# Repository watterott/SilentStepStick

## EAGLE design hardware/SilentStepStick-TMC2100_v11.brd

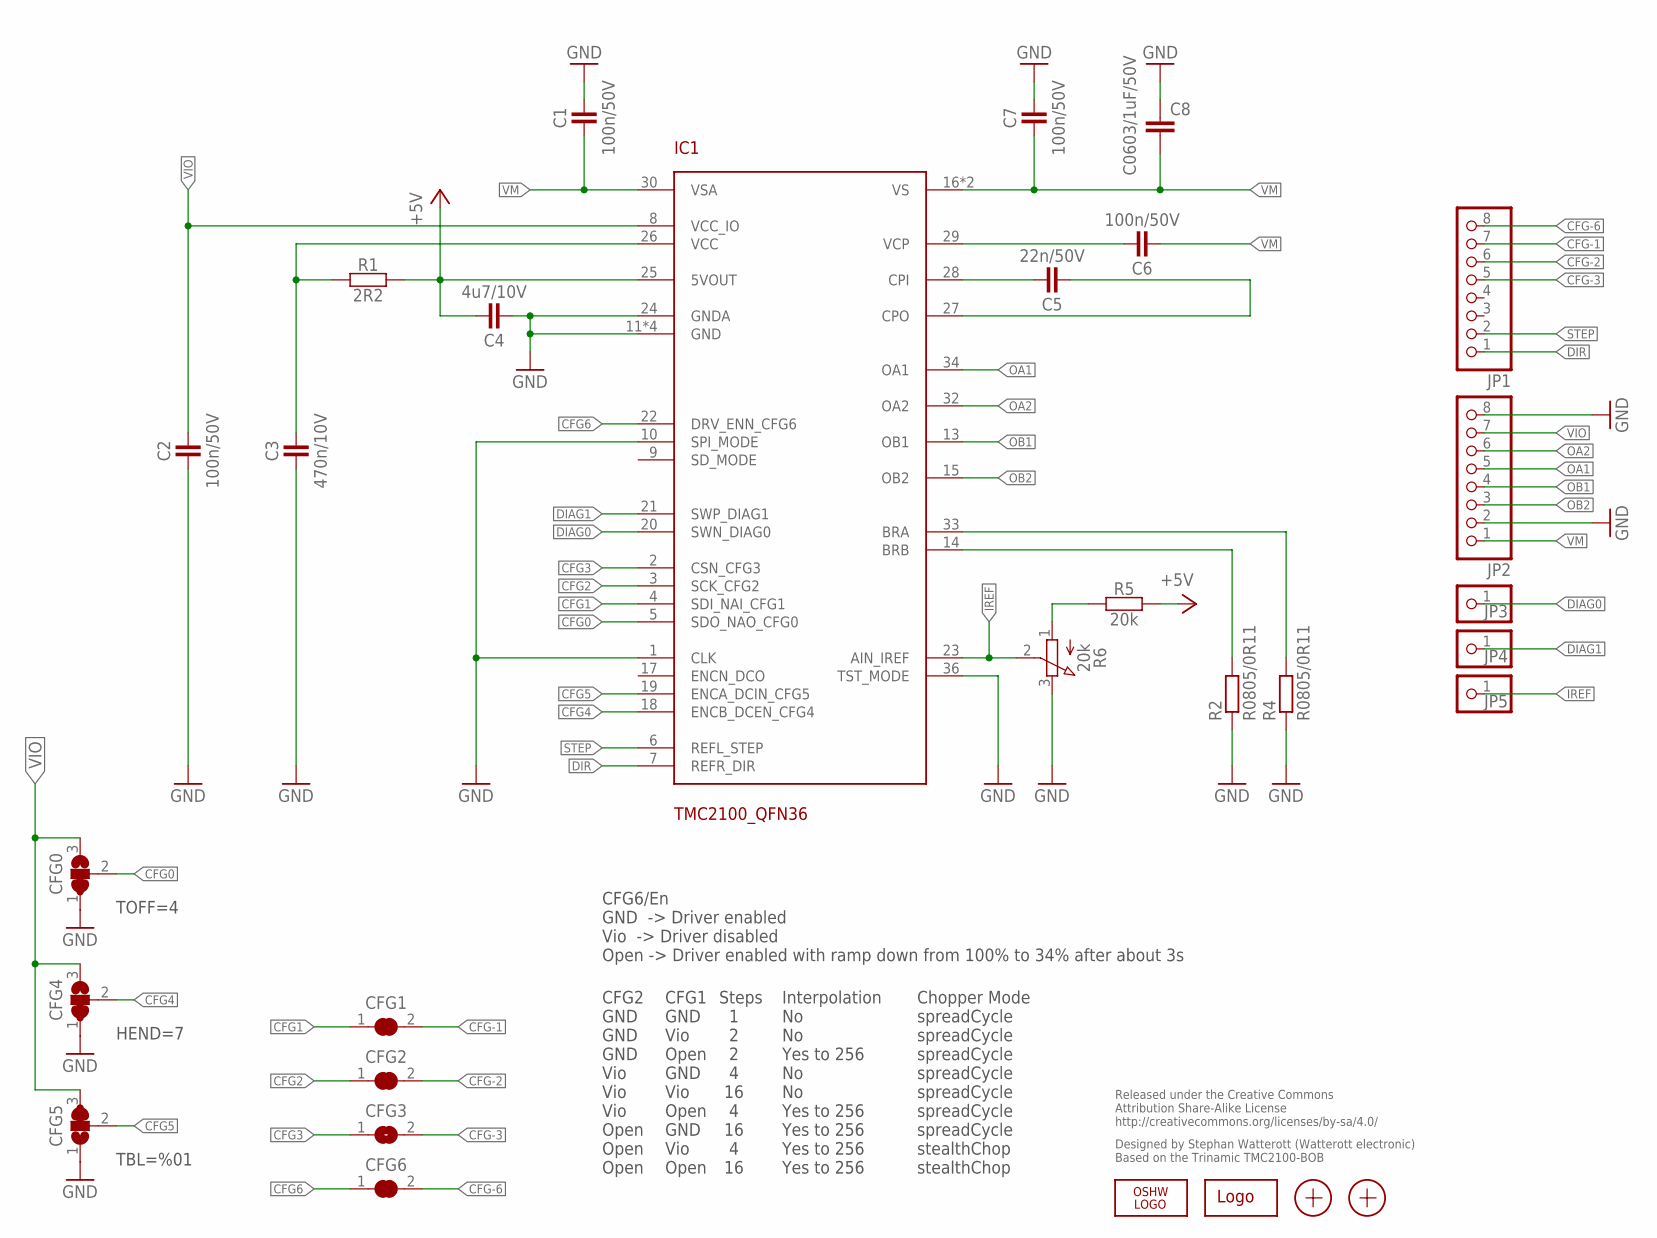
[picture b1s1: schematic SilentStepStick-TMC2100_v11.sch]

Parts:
C1, C2, C6, C7: 100n/50V; R0402
C3: 470n/10V; R0402
C4: 4u7/10V; R0402
C5: 22n/50V; R0402
C8: C0603/1uF/50V; C0603
CFG0, CFG4, CFG5: JUMPER3-0201
CFG1, CFG2, CFG3, CFG6: JUMPER2-0201
IC1: TMC2100_QFN36; QFN36
JP1, JP2: PINHD-1X08_2.54-S; 1X08-S
JP3, JP4, JP5: PINHD-1X1; 1X01
LOGO1: OSHW_LOGOX0070; OSHW_6X70
LOGO2: LOGO-S_PLACE_M; SPARK_TPLACE_M
R1: 2R2; R0402
R2, R4: R0805/0R11; M0805
R5: 20k; R0402
R6: 20k; POT_EVM3R
X1, X2: PASSER-07; PASSER_07MM

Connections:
+5V: C4.2, IC1.25 (5VOUT), R1.2, R5.2
CFG0: CFG0.2, IC1.5 (SDO_NAO_CFG0)
CFG1: CFG1.1, IC1.4 (SDI_NAI_CFG1)
CFG2: CFG2.1, IC1.3 (SCK_CFG2)
CFG3: CFG3.1, IC1.2 (CSN_CFG3)
CFG4: CFG4.2, IC1.18 (ENCB_DCEN_CFG4)
CFG5: CFG5.2, IC1.19 (ENCA_DCIN_CFG5)
CFG6: CFG6.1, IC1.22 (DRV_ENN_CFG6)
CFG-1: CFG1.2, JP1.7
CFG-2: CFG2.2, JP1.6
CFG-3: CFG3.2, JP1.5
CFG-6: CFG6.2, JP1.8
CPI: C5.2, IC1.28 (CPI)
CPO: C5.1, IC1.27 (CPO)
DIAG0: IC1.20 (SWN_DIAG0), JP3.1
DIAG1: IC1.21 (SWP_DIAG1), JP4.1
DIR: IC1.7 (REFR_DIR), JP1.1
GND: C1.2, C2.1, C3.1, C4.1, C7.2, C8.2, CFG0.1, CFG4.1, CFG5.1, IC1.1 (CLK), IC1.10 (SPI_MODE), IC1.11 (GND), IC1.12 (GND), IC1.24 (GNDA), IC1.35 (GND), IC1.36 (TST_MODE), IC1.GND_PAD (GND), JP2.2, JP2.8, R2.1, R4.1, R6.3 (E)
IREF: IC1.23 (AIN_IREF), JP5.1, R6.2 (S)
unnamed: IC1.33 (BRA), R4.2
unnamed: IC1.14 (BRB), R2.2
OA1: IC1.34 (OA1), JP2.5
OA2: IC1.32 (OA2), JP2.6
OB1: IC1.13 (OB1), JP2.4
OB2: IC1.15 (OB2), JP2.3
STEP: IC1.6 (REFL_STEP), JP1.2
VCC: C3.2, IC1.26 (VCC), R1.1
VCP: C6.2, IC1.29 (VCP)
VIO: C2.2, CFG0.3, CFG4.3, CFG5.3, IC1.8 (VCC_IO), JP2.7
VM: C1.1, C6.1, C7.1, C8.1, IC1.16 (VS), IC1.30 (VSA), IC1.31 (VS), JP2.1
VREF1: R5.1, R6.1 (A)

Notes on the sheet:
Released under the Creative Commons Attribution Share-Alike License http://creativecommons.org/licenses/by-sa/4.0/
Designed by Stephan Watterott (Watterott electronic) Based on the Trinamic TMC2100-BOB
CFG6/En GND -> Driver enabled Vio -> Driver disabled Open -> Driver enabled with ramp down from 100% to 34% after about 3s
CFG2 GND GND GND Vio Vio Vio Open Open Open
CFG1 GND Vio Open GND Vio Open GND Vio Open
Steps 1 2 2 4 16 4 16 4 16
Interpolation No No Yes to 256 No No Yes to 256 Yes to 256 Yes to 256 Yes to 256
Chopper Mode spreadCycle spreadCycle spreadCycle spreadCycle spreadCycle spreadCycle spreadCycle stealthChop stealthChop
TOFF=4
HEND=7
TBL=%01

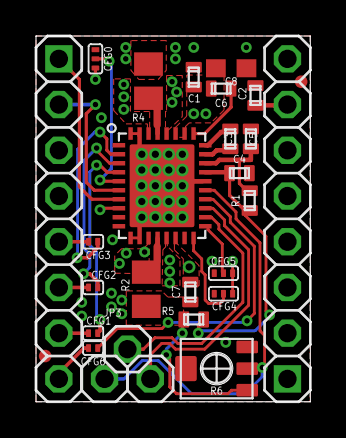
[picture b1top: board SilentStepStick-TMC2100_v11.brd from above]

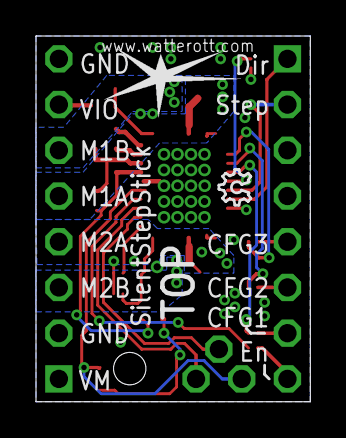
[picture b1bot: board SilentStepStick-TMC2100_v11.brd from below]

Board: 4 copper layers, 15.2 x 20.3 mm, 30 parts (2 on the bottom side), 31 nets.

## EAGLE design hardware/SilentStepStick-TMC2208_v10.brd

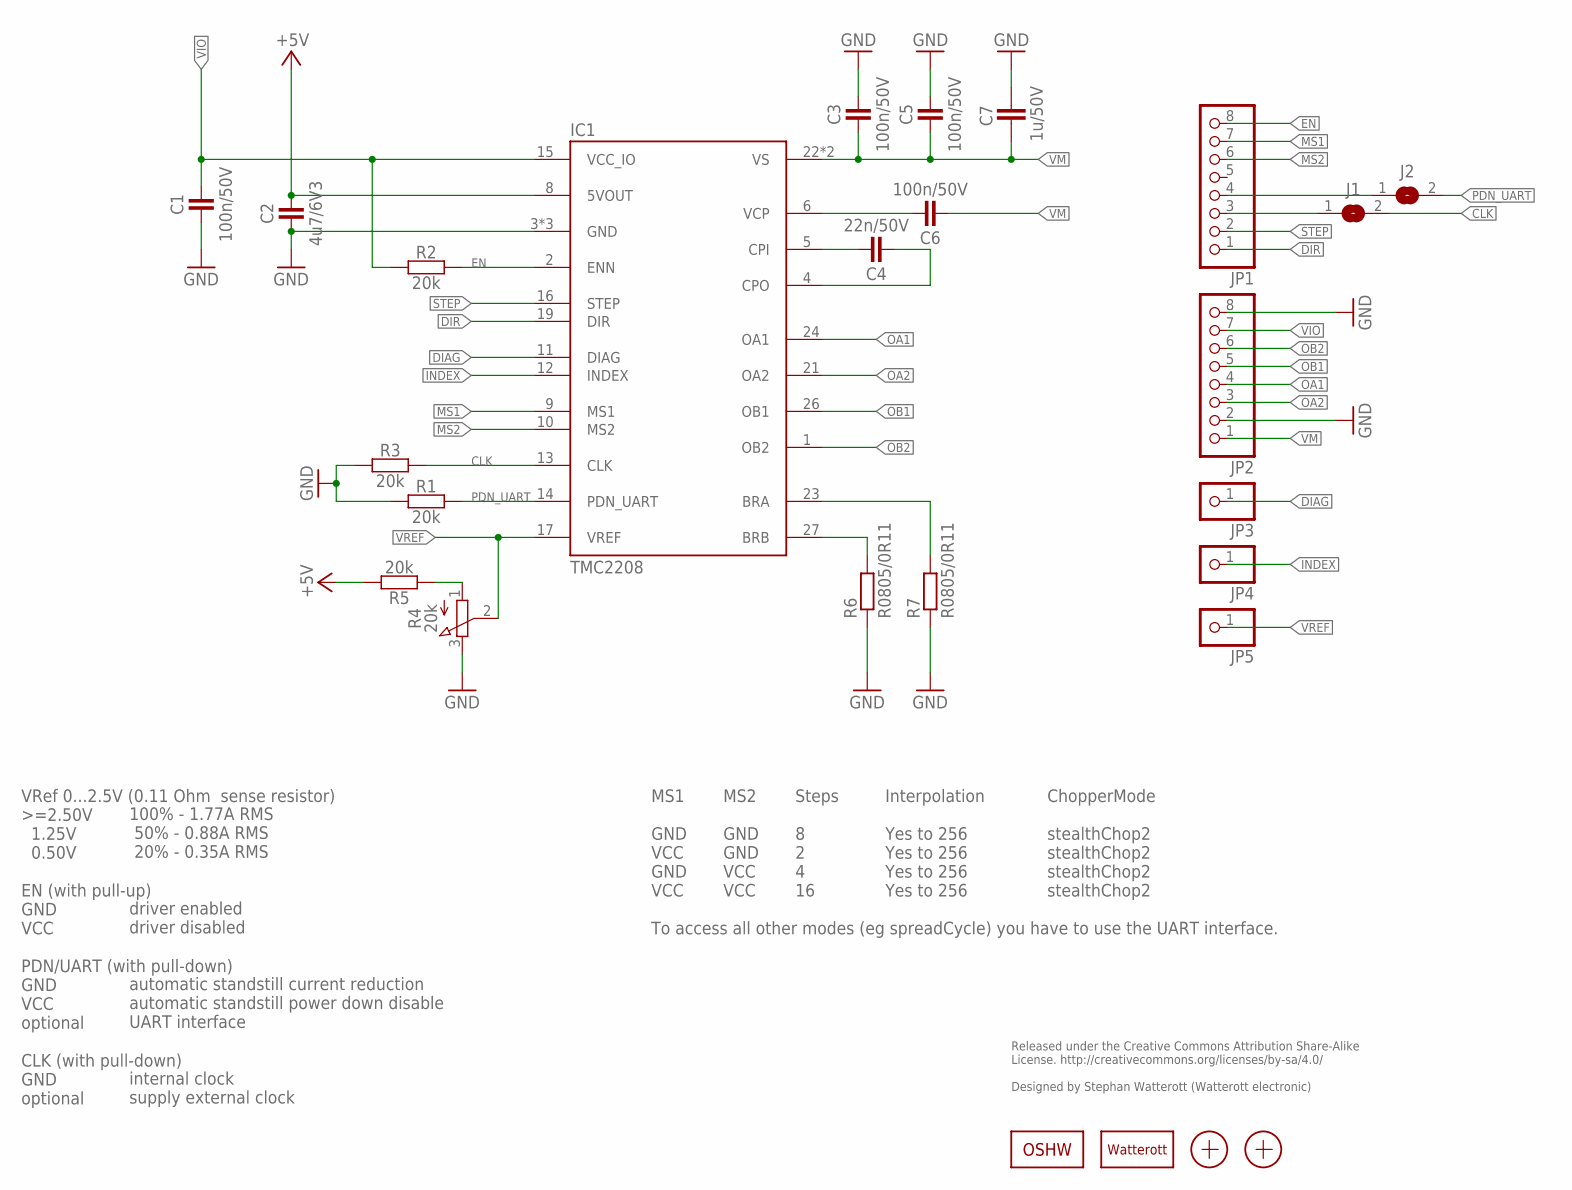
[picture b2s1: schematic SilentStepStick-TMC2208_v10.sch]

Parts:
C1, C3, C5, C6: 100n/50V; C0402
C2: 4u7/6V3; C0402
C4: 22n/50V; C0402
C7: 1u/50V; C0805
IC1: TMC2208; QFN28-PAD
J1, J2: JUMPER2-0402
JP1, JP2: PINHD-1X08_2.54-S; 1X08-S
JP3, JP4, JP5: PINHD-1X1; 1X01
LOGO1: OSHW_LOGOX0070; OSHW_6X70
LOGO2: LOGO-S_PLACE_M; SPARK_TPLACE_M
R1, R2, R3, R5: 20k; C0402
R4: 20k; POT_EVM3R
R6, R7: R0805/0R11; M0805
X1, X2: PASSER-04; PASSER_04MM

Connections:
+5V: C2.2, IC1.8 (5VOUT), R5.2
BRA: IC1.23 (BRA), R7.2
BRB: IC1.27 (BRB), R6.2
CLK: IC1.13 (CLK), J1.2, R3.2
CPI: C4.2, IC1.5 (CPI)
CPO: C4.1, IC1.4 (CPO)
DIAG: IC1.11 (DIAG), JP3.1
DIR: IC1.19 (DIR), JP1.1
EN: IC1.2 (ENN), JP1.8, R2.2
GND: C1.1, C2.1, C3.2, C5.2, C7.2, IC1.3 (GND), IC1.18 (GND), IC1.TP (GND), JP2.2, JP2.8, R1.1, R3.1, R4.3 (E), R6.1, R7.1
INDEX: IC1.12 (INDEX), JP4.1
MS1: IC1.9 (MS1), JP1.7
MS2: IC1.10 (MS2), JP1.6
unnamed: J1.1, JP1.3
unnamed: J2.1, JP1.4
OA1: IC1.24 (OA1), JP2.4
OA2: IC1.21 (OA2), JP2.3
OB1: IC1.26 (OB1), JP2.5
OB2: IC1.1 (OB2), JP2.6
PDN_UART: IC1.14 (PDN_UART), J2.2, R1.2
STEP: IC1.16 (STEP), JP1.2
VCP: C6.2, IC1.6 (VCP)
VIO: C1.2, IC1.15 (VCC_IO), JP2.7, R2.1
VM: C3.1, C5.1, C6.1, C7.1, IC1.22 (VS), IC1.28 (VS), JP2.1
VREF: IC1.17 (VREF), JP5.1, R4.2 (S)
VREF1: R4.1 (A), R5.1

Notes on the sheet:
Released under the Creative Commons Attribution Share-Alike License. http://creativecommons.org/licenses/by-sa/4.0/ Designed by Stephan Watterott (Watterott electronic)
VRef 0...2.5V (0.11 Ohm sense resistor) >=2.50V 1.25V 0.50V EN (with pull-up) GND VCC PDN/UART (with pull-down) GND VCC optional CLK (with pull-down) GND optional
100% - 1.77A RMS 50% - 0.88A RMS 20% - 0.35A RMS driver enabled driver disabled automatic standstill current reduction automatic standstill power down disable UART interface internal clock supply external clock
MS1 GND VCC GND VCC To access all other modes (eg spreadCycle) you have to use the UART interface.
MS2 GND GND VCC VCC
Steps 8 2 4 16
Interpolation Yes to 256 Yes to 256 Yes to 256 Yes to 256
ChopperMode stealthChop2 stealthChop2 stealthChop2 stealthChop2

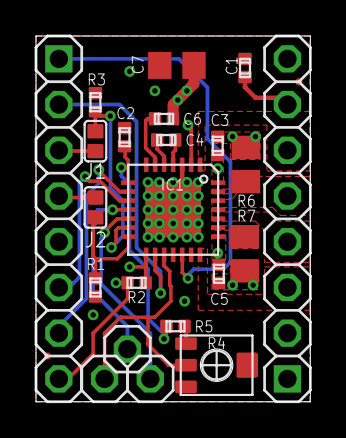
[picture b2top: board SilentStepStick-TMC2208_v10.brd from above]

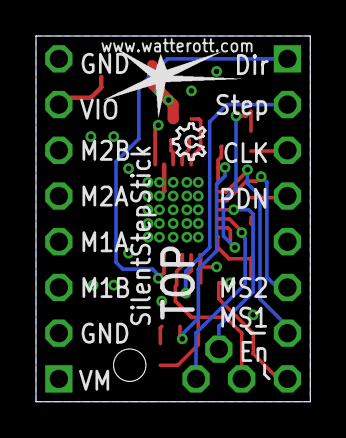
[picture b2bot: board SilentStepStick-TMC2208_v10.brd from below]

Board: 4 copper layers, 15.2 x 20.3 mm, 26 parts (2 on the bottom side), 26 nets.
